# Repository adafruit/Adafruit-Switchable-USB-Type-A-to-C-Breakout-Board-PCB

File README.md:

## Adafruit Switchable USB Type A to C Breakout Board PCB

<a href="http://www.adafruit.com/products/5972"><br/>
Click here to purchase one from the Adafruit shop</a>

PCB files for the Adafruit Switchable USB Type A to C Breakout Board. 

Format is EagleCAD schematic and board layout
* https://www.adafruit.com/product/5972

### Description

We don't quite know what to call this doohicky - some folks refer to it as a [USB Condom](https://int3.cc/products/usbcondoms) but that's specifically for when the data lines on a USB port are disabled so that a device charges without data access. This board is a little more advanced: you can manually switch each of the 4 wires on or off for a variety of uses:

* If you want to have a 'charge only' device, simply switch the D+ and D- lines off
* For power monitoring, you can do high side (disable the V+ line) or low side (disable the GND line)
* For tapping into the USB signal, or monitoring the power voltage, keep all the switches on and probe the labelled pads on either side

With the onboard 4-DIP switch, you can flip to your heart's content. Only thing to note is the [C&K SDA04H1SBD](https://www.ckswitches.com/media/1327/sda.pdf) switches are technically rated for 5V 100mA  so we designed this for low-current-draw microcontroller project board hacking. (You could probably go a bit higher but don't tell anyone!)

### License

Adafruit invests time and resources providing this open source design, please support Adafruit and open-source hardware by purchasing products from [Adafruit](https://www.adafruit.com)!

Designed by Limor Fried/Ladyada for Adafruit Industries.

Creative Commons Attribution/Share-Alike, all text above must be included in any redistribution. 
See license.txt for additional details.

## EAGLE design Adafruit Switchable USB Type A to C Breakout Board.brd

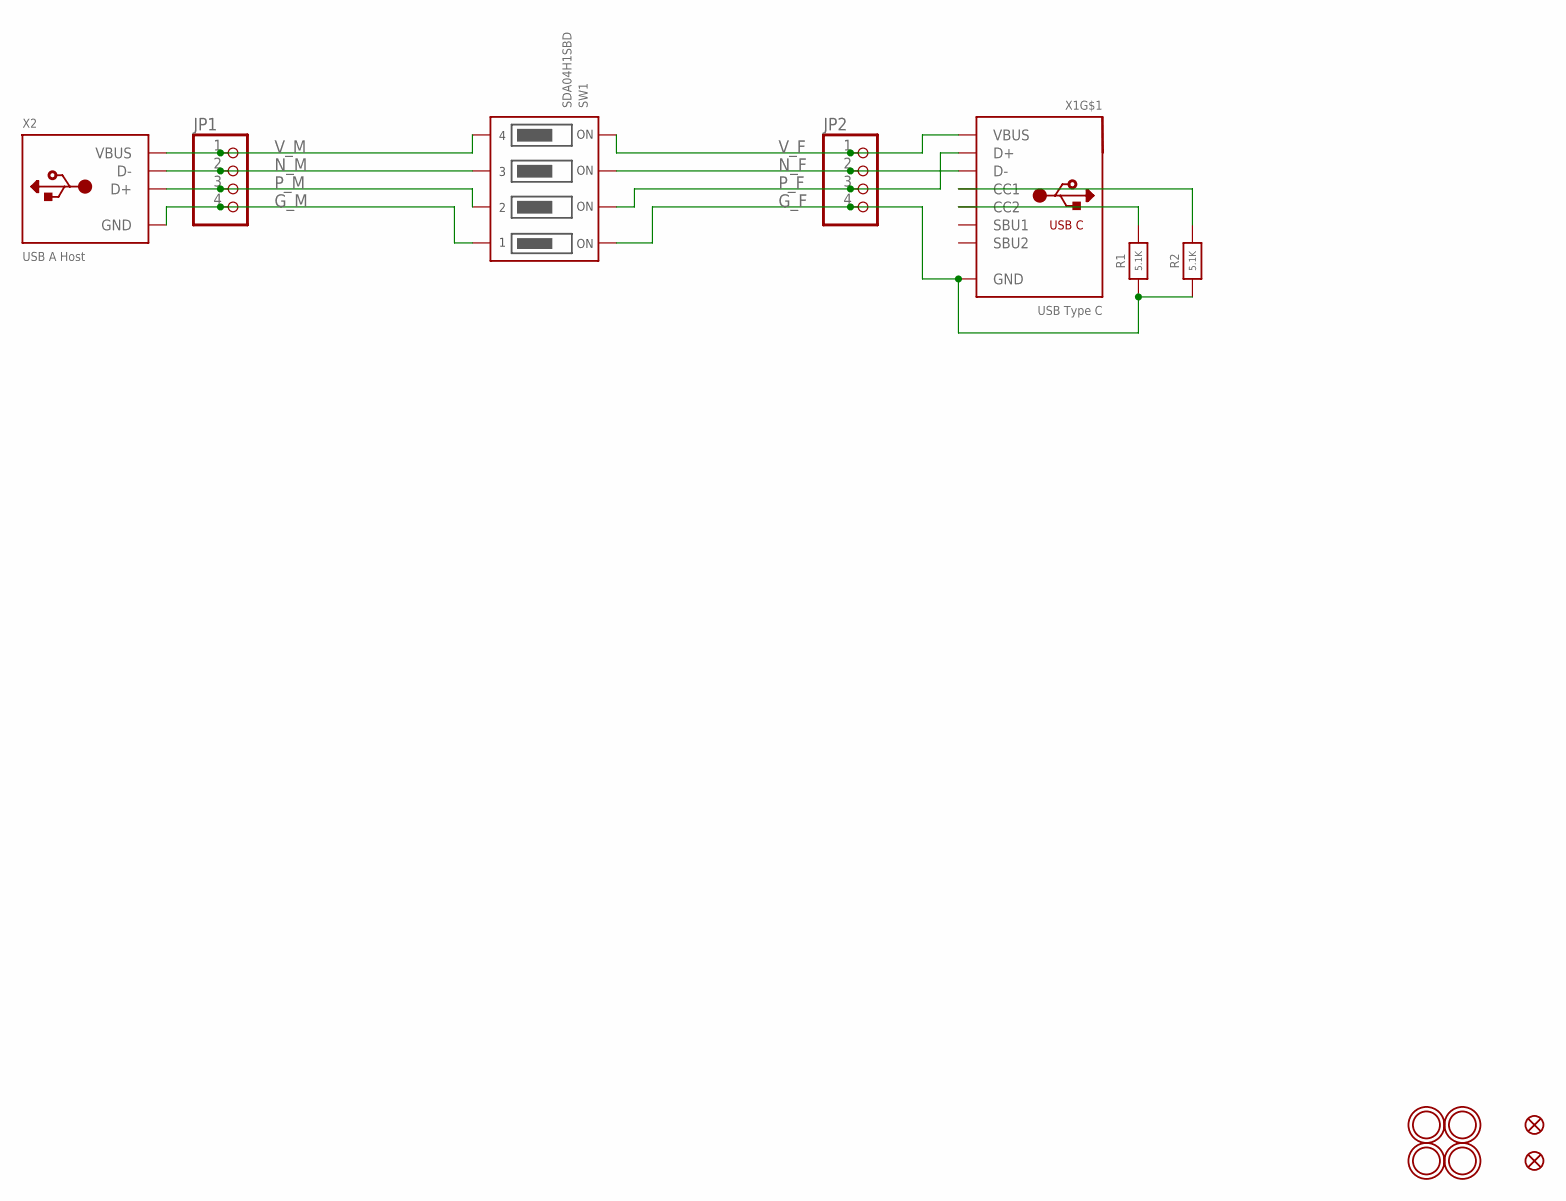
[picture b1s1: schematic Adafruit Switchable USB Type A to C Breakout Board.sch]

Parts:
FID1, FID2: FIDUCIAL_1MM
JP1, JP2: HEADER-1X4ROUND; 1X04_ROUND
R1, R2: 5.1K; 0603-NO
SW1: SDA04H1SBD; DIPSWITCH_4PIN
U$1, U$2, U$3, U$4: MOUNTINGHOLE2.5; MOUNTINGHOLE_2.5_PLATED
X1: USB Type C; USB_C_CUSB31-CFM2AX-01-X
X2: USB A Host; USB_HOST-PTH

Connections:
G_F: JP2.4, R1.1, R2.1, SW1.1ON, X1.A1B12 (GND), X1.B1A12 (GND)
G_M: JP1.4, SW1.1OFF, X2.GND
unnamed: R1.2, X1.B5 (CC2)
unnamed: R2.2, X1.A5 (CC1)
N_F: JP2.2, SW1.3ON, X1.A7 (D-), X1.B7 (D-)
N_M: JP1.2, SW1.3OFF, X2.D-
P_F: JP2.3, SW1.2ON, X1.A6 (D+), X1.B6 (D+)
P_M: JP1.3, SW1.2OFF, X2.D+
V_F: JP2.1, SW1.4ON, X1.A4B9 (VBUS), X1.B4A9 (VBUS)
V_M: JP1.1, SW1.4OFF, X2.VBUS

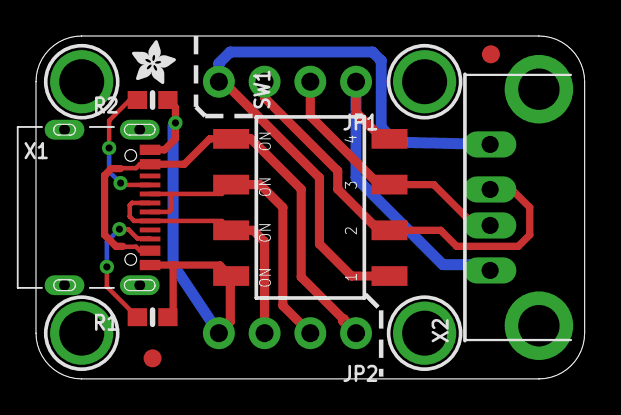
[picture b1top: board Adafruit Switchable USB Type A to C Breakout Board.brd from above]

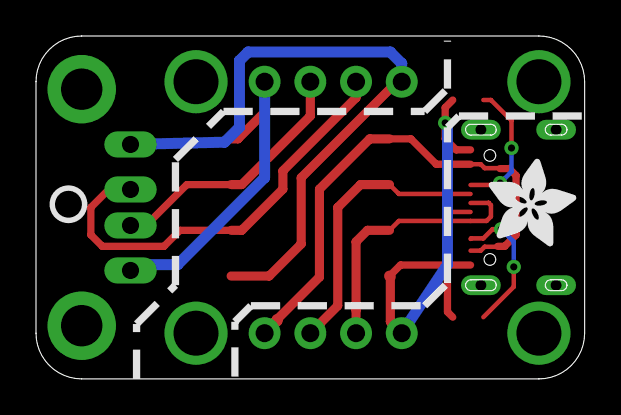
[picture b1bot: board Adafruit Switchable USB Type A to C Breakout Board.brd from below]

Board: 2 copper layers, 30.5 x 19.1 mm, 41 parts (11 on the bottom side), 10 nets.

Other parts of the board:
PLABEL0: PLABEL0
PLABEL1: PLABEL1
PLABEL2: PLABEL2
PLABEL3: PLABEL3
PLABEL4: PLABEL4
PLABEL5: PLABEL5
PLABEL6: PLABEL6
PLABEL7: PLABEL7
PLABEL8: PLABEL8
PLABEL9: PLABEL9
PLABEL10: PLABEL10
PLABEL11: PLABEL11
PLABEL12: PLABEL12
PLABEL13: PLABEL13
PLABEL14: PLABEL14
PLABEL15: PLABEL15
PLABEL16: PLABEL16
PLABEL17: PLABEL17
PLABEL18: PLABEL18
PLABEL19: PLABEL19
PLABEL20: PLABEL20
PLABEL21: PLABEL21
PLABEL22: PLABEL22
PLABEL23: PLABEL23
PLABEL24: PLABEL24
U$5: ADAFRUIT_2.5MM
U$6: ADAFRUIT_5MM
U$8: PCBFEAT-REV-040

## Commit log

2024-06-06 cookiecutter
2024-06-06 PCB files

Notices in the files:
parts and their libraries:
microbuilder: This work is placed in the public domain, and may be freely used for commercial and non-commercial work with the following conditions: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
